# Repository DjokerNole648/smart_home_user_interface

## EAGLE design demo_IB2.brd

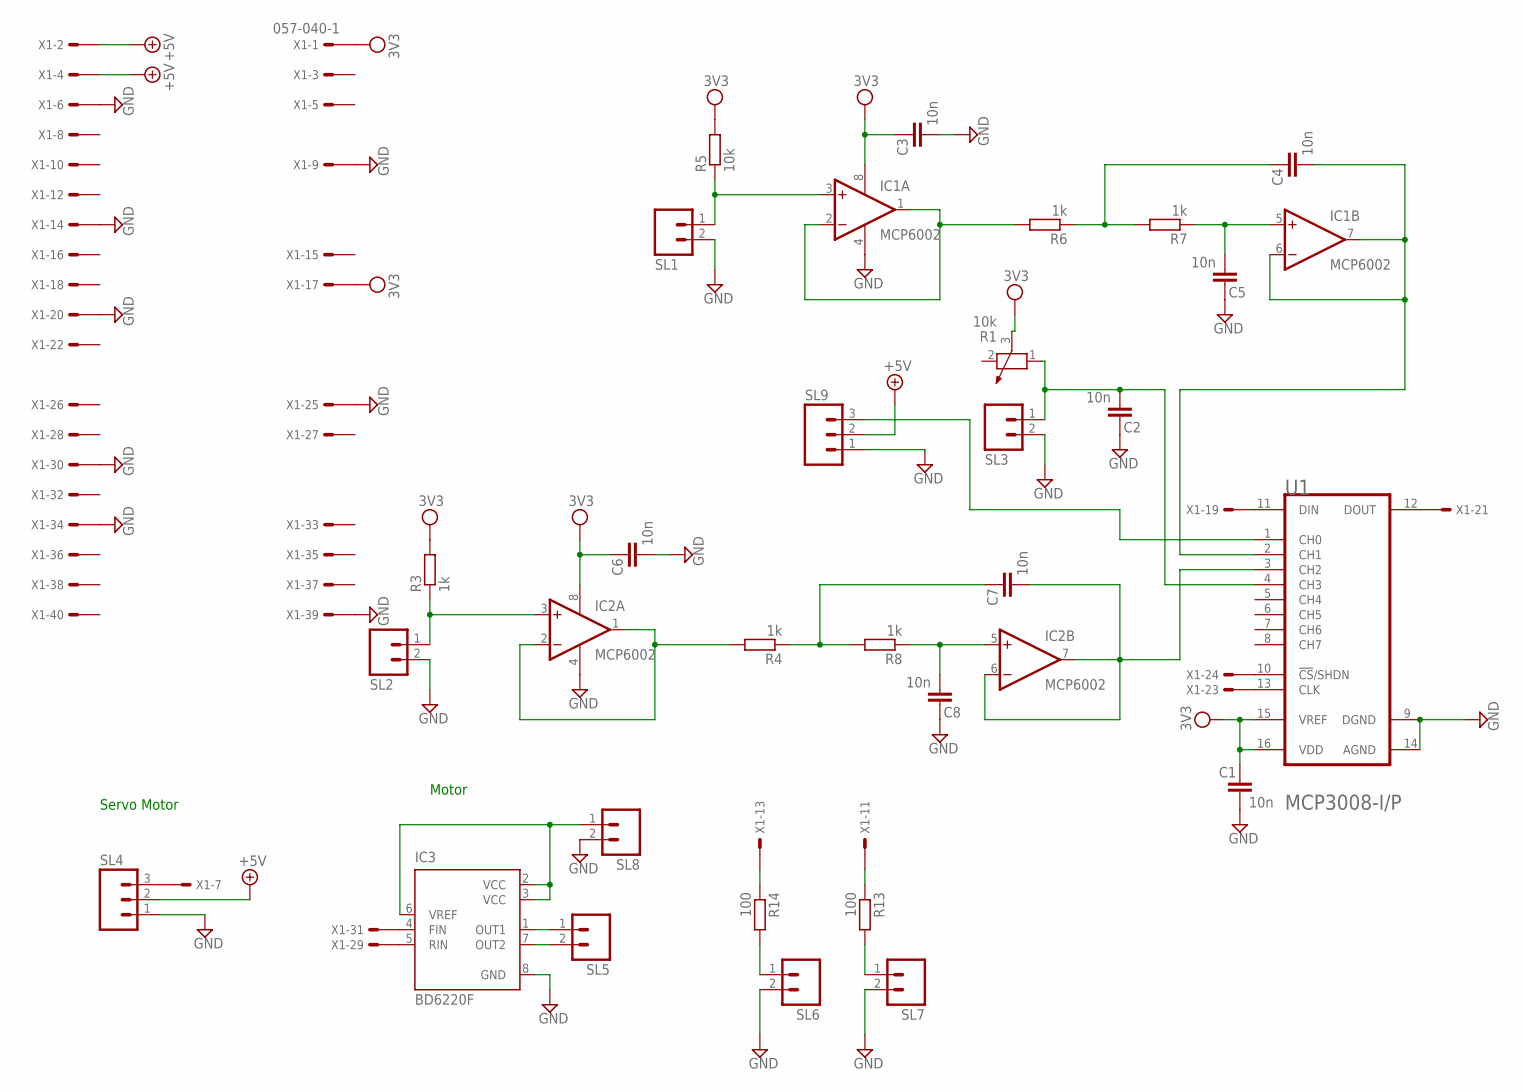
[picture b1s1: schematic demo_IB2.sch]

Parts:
C1, C2, C3, C4, C5, C6, C7, C8: 10n; C0805
IC1, IC2: MCP6002; SO08
IC3: BD6220F; SOP8
R1: 10k; PT-10
R3, R4, R6, R7, R8: 1k; R0805
R5: 10k; R0805
R13, R14: 100; R0805
SL1, SL2, SL3, SL5, SL6, SL7, SL8: M02; 02P
SL4, SL9: M03; 03P
U1: MICROCHIP_MCP3008-I-P; SO-16
X1: 057-040-1

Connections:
+5V: SL4.2, SL9.2, X1.2, X1.4
GND: C1.2, C2.1, C3.2, C5.1, C6.2, C8.1, IC1.4 (V-), IC2.4 (V-), IC3.8 (GND), SL1.2, SL2.2, SL3.2, SL4.1, SL6.2, SL7.2, SL8.2, SL9.1, U1.9 (DGND), U1.14 (AGND), X1.6, X1.9, X1.14, X1.20, X1.25, X1.30, X1.34, X1.39
unnamed: C2.2, R1.1, SL3.1, U1.4 (CH3)
unnamed: IC2.3 (+IN), R3.1, SL2.1
unnamed: IC2.1 (OUT), IC2.2 (-IN), R4.2
unnamed: C7.2, IC2.6 (-IN), IC2.7 (OUT), U1.3 (CH2)
unnamed: IC1.3 (+IN), R5.1, SL1.1
unnamed: IC1.1 (OUT), IC1.2 (-IN), R6.2
unnamed: U1.11 (DIN), X1.19
unnamed: U1.12 (DOUT), X1.21
unnamed: U1.13 (CLK), X1.23
unnamed: U1.10 (!CS!/SHDN), X1.24
unnamed: C4.2, IC1.6 (-IN), IC1.7 (OUT), U1.2 (CH1)
unnamed: C4.1, R6.1, R7.2
unnamed: C7.1, R4.1, R8.2
unnamed: C5.2, IC1.5 (+IN), R7.1
unnamed: C8.2, IC2.5 (+IN), R8.1
unnamed: SL9.3, U1.1 (CH0)
unnamed: IC3.2 (VCC), IC3.3 (VCC), IC3.6 (VREF), SL8.1
unnamed: IC3.5 (RIN), X1.29
unnamed: IC3.4 (FIN), X1.31
unnamed: SL4.3, X1.7
unnamed: IC3.1 (OUT1), SL5.1
unnamed: R14.2, SL6.1
unnamed: R14.1, X1.13
unnamed: R13.2, SL7.1
unnamed: R13.1, X1.11
unnamed: IC3.7 (OUT2), SL5.2
VCC: C1.1, C3.1, C6.1, IC1.8 (V+), IC2.8 (V+), R1.3, R3.2, R5.2, U1.15 (VREF), U1.16 (VDD), X1.1, X1.17

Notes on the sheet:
Motor
Servo Motor

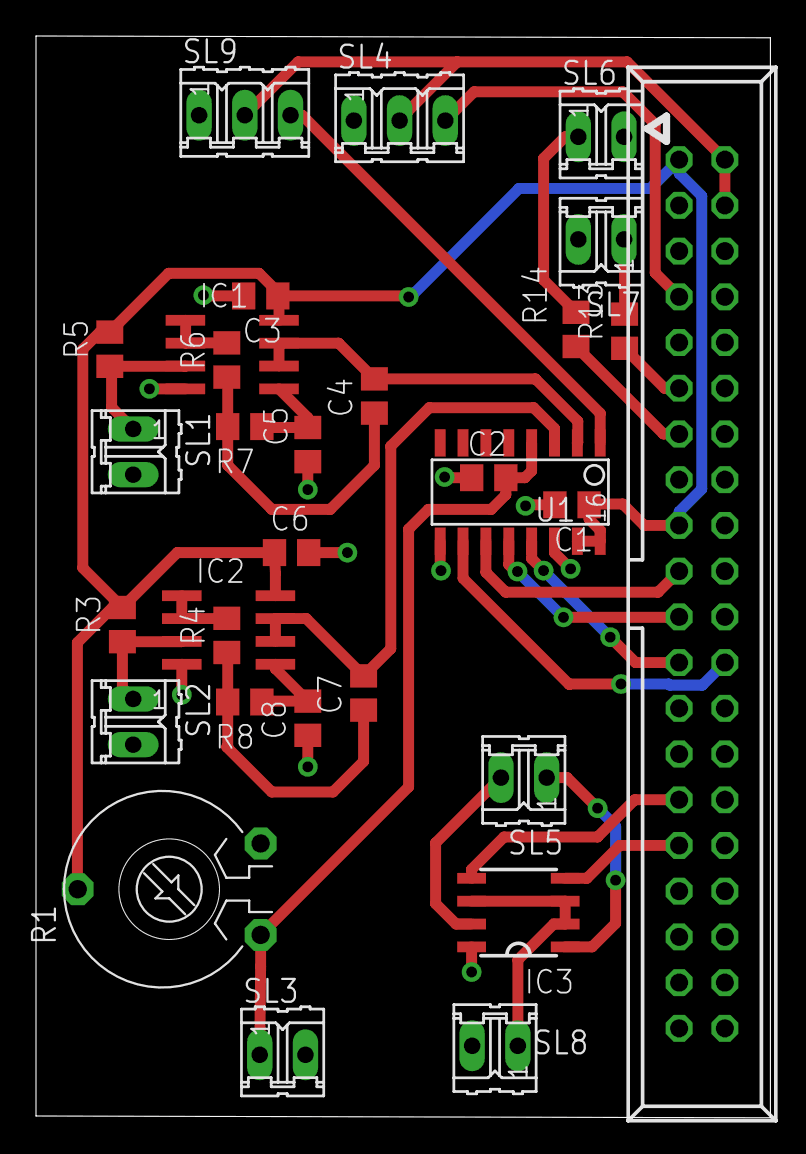
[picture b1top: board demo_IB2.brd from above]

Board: 2 copper layers, 40.8 x 60.1 mm, 31 parts (0 on the bottom side), 29 nets.

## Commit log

2022-03-26 v3, title of loginPage to be set
2022-03-27 v4, settled
